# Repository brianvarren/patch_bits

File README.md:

# patch_bits

**SDIY building blocks.** Tiny helper boards that that make quick prototyping fun and easy.

---

## What is this?

A growing collection of hardware abstractions for recurring problems in mixed-signal synth DIY. My intent is to provide simple touch points: inputs, outputs, power, ground. Everything else should be refined, reliable boilerplate. Being fully open-hardware, these helpers can become reusable design blocks, to be implemented in larger custom synth PCBs or modules as you (or I) see fit.

---

## Philosophy

- Open-source hardware (CERN-OHL-W)
- Built for speed, not purity
- Easy to chain, mount, and mod

---

## A Note on Voltage & Signal Standards

For my personal builds, I decided some time ago to eschew Eurorack dual-rail power supplies and 10Vpp bipolar signals in favor of unipolar 0-3.3V DC-coupled MCU-friendly signals. I did this both out of frustration and laziness. My aim is to prototype quickly, learn in the process, and most of all, have fun. I found myself spending more time designing and debugging analog pre- and post- stages than I did designing the synths themselves. Some may argue that that is an important part of synth design; I can't argue. But, to me, a simplified, unipolar 3.3V signal format represents the freedom to explore without boundaries.

These helpers are designed to be compatible with both 3.3V and 5V systems. They may work with other single-rail voltages too (check the datasheets of the individual components).

Adapting to dual-rail supplies would require significant rework in most cases.

---

## Use it

- Build your own from the files
- Order from JLC
- Or [buy a prebuilt one](#) if you’re lazy or busy (no shame)

---

## License

CERN-OHL-W v2  
If you make changes and share them, cool. If you don’t, don’t sell them.

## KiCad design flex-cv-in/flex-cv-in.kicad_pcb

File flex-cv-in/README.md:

# Patch Bits: flex-cv-in

This board solves one big problem, and takes care of a handful of smaller ones along the way.

The big one is that RP2040 only gives you four ADC channels. That’s enough until you start designing synth modules and suddenly wish you had four CV inputs, each with a knob to offset or dial in a parameter manually. That’s the itch this board scratches.

flex-cv-in provides a footprint for a jack and a potentiometer. The knob and incoming CV are resistively summed into an inverting op-amp biased at mid-rail. The feedback resistor sets the gain to 2, restoring the original CV amplitude after averaging. The result is a stable, centered voltage where the knob sets a baseline and the CV input adds (or subtracts) modulation. That single output feeds one ADC channel.

Schottky diode clamps protect against over-voltage. There’s a dedicated jack detect pin designed for microcontrollers—pulled low when nothing’s inserted, floating high when a jack is present.

By default, the board runs in “bias” mode, which is ideal for parameters you want to sweep and modulate. But with two solder jumpers and a trace cut, you can reconfigure it into an attenuate mode. In that setup, the knob scales the incoming CV instead, centered around mid-rail. This is useful for things like linear FM, but the utility doesn’t stop there.

The board includes a low-pass RC filter on the output by default to tame ADC noise. If you want raw edges and wideband modulation, a labeled trace cut lets you disable that filter easily—no desoldering required.

It’s built for 3.3V or 5V single-supply systems, with short analog paths, proper biasing, and clean routing. It’s not calibrated, not meant for bipolar Eurorack signals, and not trying to be fancy. It just works—and it stays out of your way when you want to get creative.

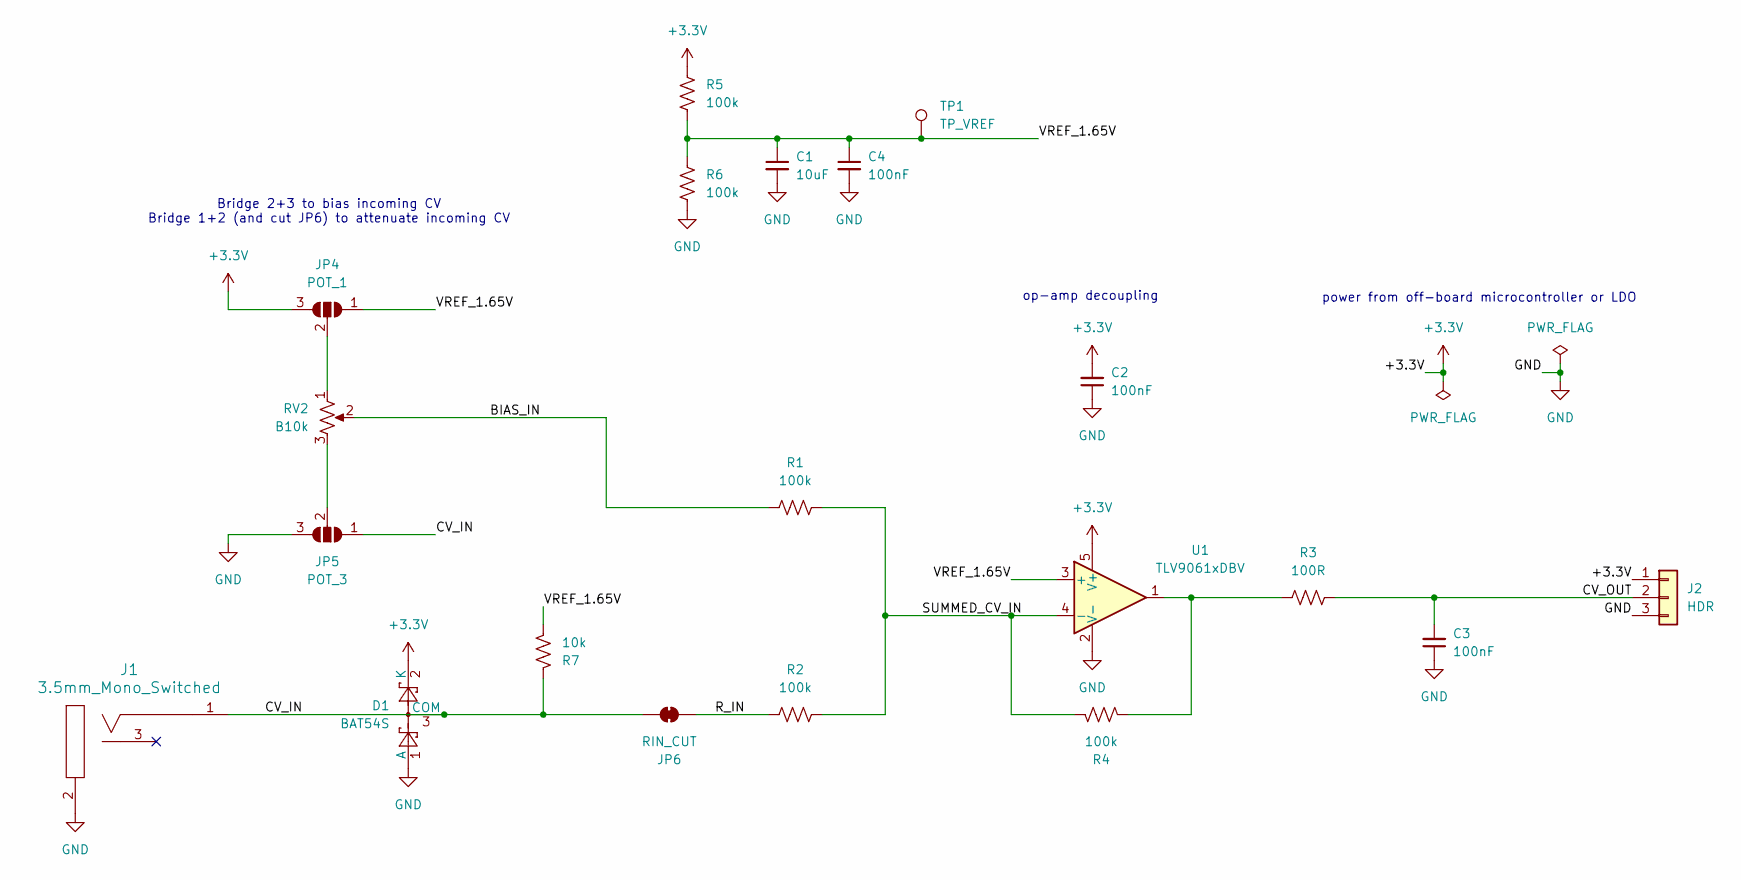
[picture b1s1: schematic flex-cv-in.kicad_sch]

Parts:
C1: 10uF; C_0805_2012Metric
C2, C3, C4: 100nF; C_0805_2012Metric
D1: BAT54S; SOT-23
J1: 3.5mm_Mono_Switched; EighthInch_PJ398SM; Part Number WQP-WQP518MA
J2: HDR; PinSocket_1x03_P2.54mm_Vertical
JP4: POT_1; SolderJumper-3_P1.3mm_Open_RoundedPad1.0x1.5mm
JP5: POT_3; SolderJumper-3_P1.3mm_Open_RoundedPad1.0x1.5mm
JP6: RIN_CUT; SolderJumper-2_P1.3mm_Bridged_RoundedPad1.0x1.5mm
R1, R2, R4, R5, R6: 100k; R_0805_2012Metric
R3: 100R; R_0805_2012Metric
R7: 10k; R_0805_2012Metric
RV2: B10k; Pot_9mm_Knurl_NoDet
TP1: TP_VREF; TestPoint_Pad_D1.5mm
U1: TLV9061xDBV; SOT-23-5

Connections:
+3.3V: C2.2, D1.2 (K), J2.1, JP4.3 (B), R5.1, U1.5 (V+)
/BIAS_IN: R1.1, RV2.2
/CV_IN: D1.3 (COM), J1.1 (SIG), JP5.1 (A), JP6.2 (B), R7.2
/CV_OUT: C3.2, J2.2, R3.2
/R_IN: JP6.1 (A), R2.1
/SUMMED_CV_IN: R1.2, R2.2, R4.1, U1.4 (-)
/VREF_1.65V: C1.1, C4.1, JP4.1 (A), R5.2, R6.1, R7.1, TP1.1, U1.3 (+)
GND: C1.2, C2.1, C3.1, C4.2, D1.1 (A), J1.2 (SHEILD), J2.3, JP5.3 (B), R6.2, U1.2 (V-)
unnamed: JP4.2 (C), RV2.1
unnamed: JP5.2 (C), RV2.3
unnamed: R3.1, R4.2, U1.1

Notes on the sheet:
op-amp decoupling
power from off-board microcontroller or LDO
Bridge 2+3 to bias incoming CV Bridge 1+2 (and cut JP6) to attenuate incoming CV

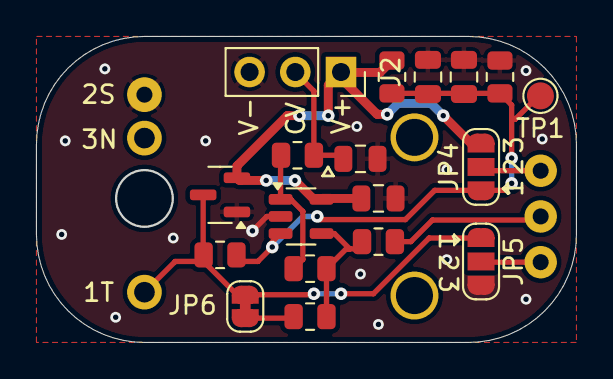
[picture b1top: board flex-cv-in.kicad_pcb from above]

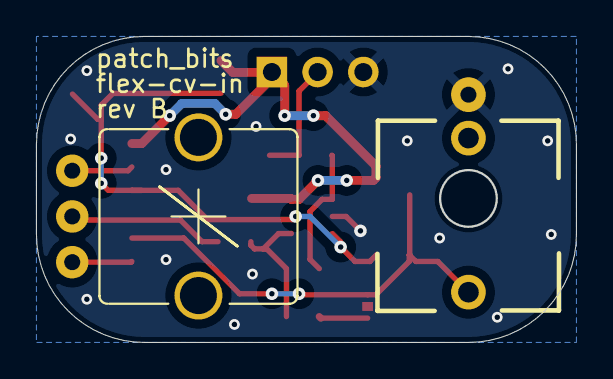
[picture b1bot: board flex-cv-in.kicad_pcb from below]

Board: 2 copper layers, 29.9 x 16.9 mm, 20 parts (2 on the bottom side), 11 nets.

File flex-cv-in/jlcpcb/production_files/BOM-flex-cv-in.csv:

Comment,Designator,Footprint,LCSC,Quantity
100k,R4,R_0805_2012Metric,,1
100nF,C3,C_0805_2012Metric,,1
HDR,J2,PinSocket_1x03_P2.54mm_Vertical,,1
10uF,C1,C_0805_2012Metric,,1
100k,R5,R_0805_2012Metric,,1
100k,R2,R_0805_2012Metric,,1
TLV9061xDBV,U1,SOT-23-5,,1
100k,R6,R_0805_2012Metric,,1
100nF,C2,C_0805_2012Metric,,1
BAT54S,D1,SOT-23,,1
100R,R3,R_0805_2012Metric,,1
100k,R1,R_0805_2012Metric,,1
100nF,C4,C_0805_2012Metric,,1
10k,R7,R_0805_2012Metric,,1

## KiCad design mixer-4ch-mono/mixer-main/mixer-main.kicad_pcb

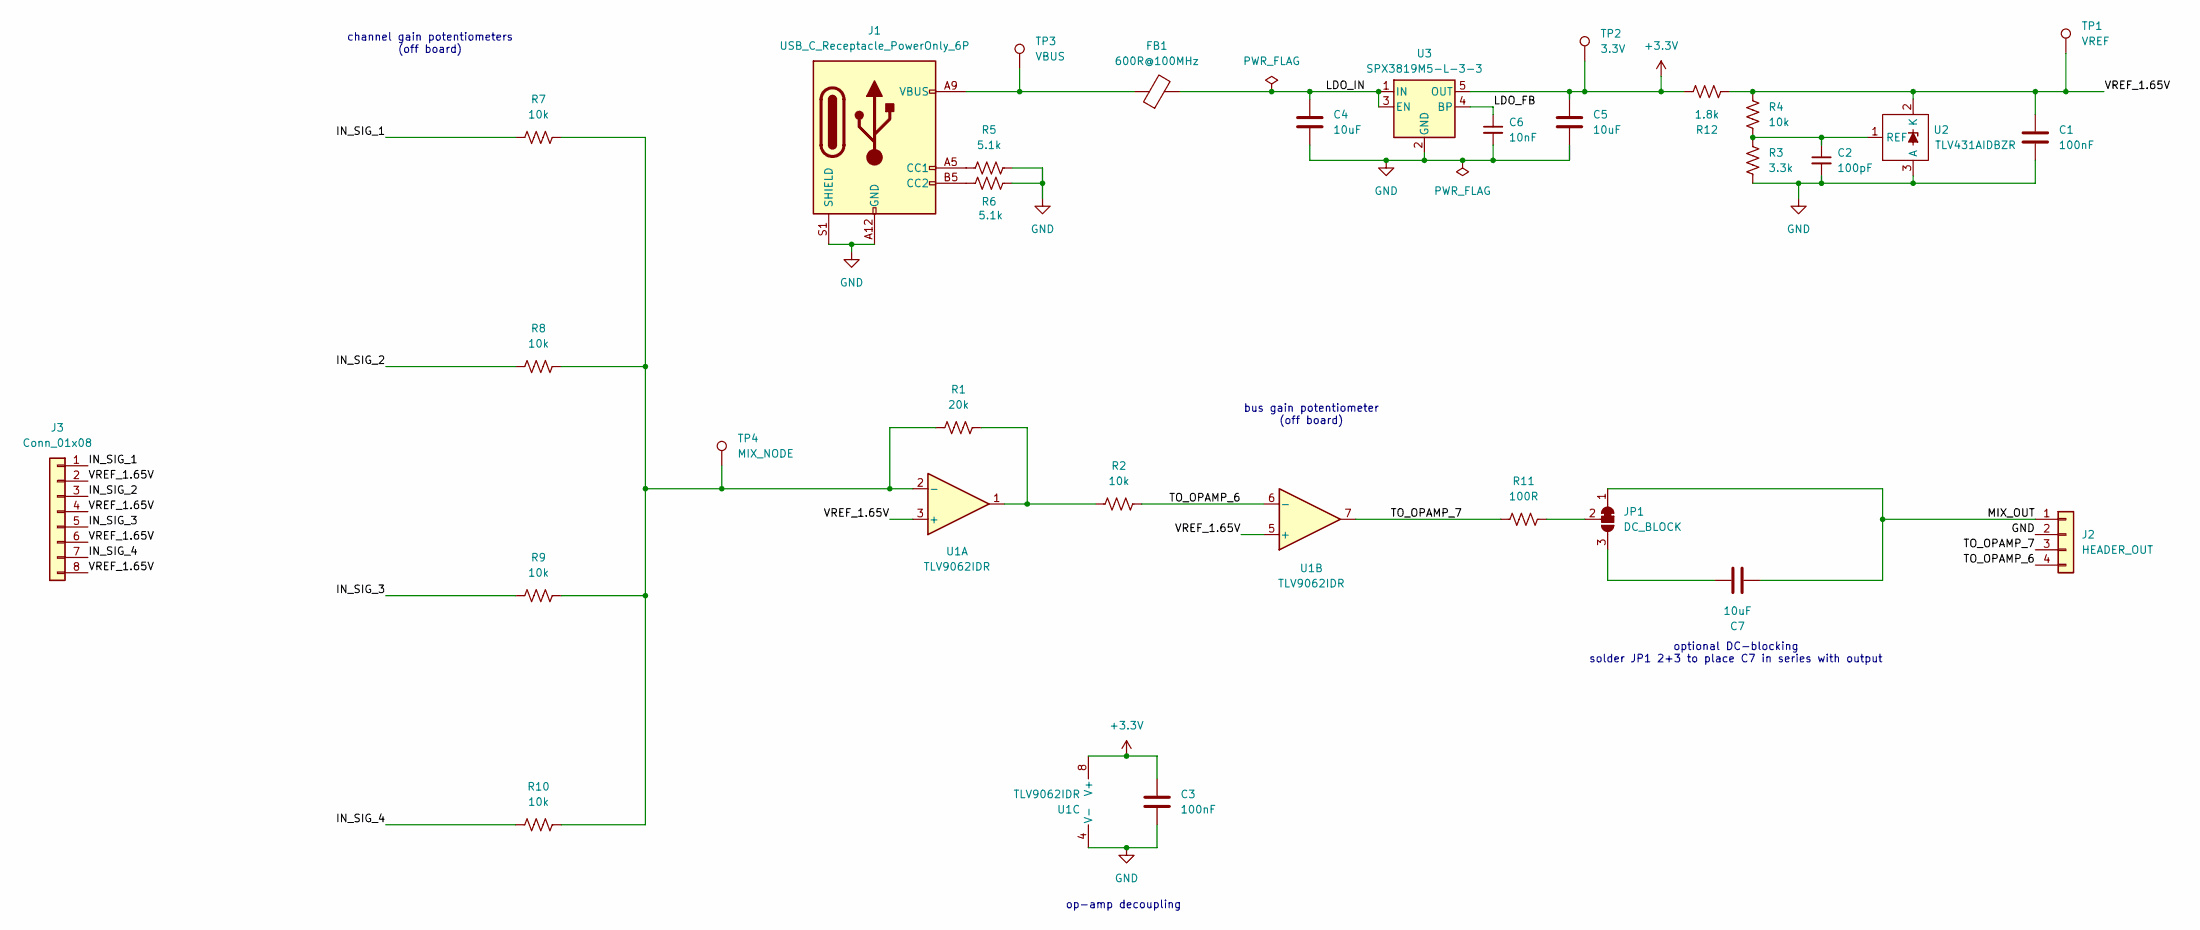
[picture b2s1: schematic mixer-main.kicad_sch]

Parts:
C1, C3: 100nF; C_0603_1608Metric
C2: 100pF; C_0603_1608Metric
C4, C5, C7: 10uF; C_1206_3216Metric
C6: 10nF; C_0805_2012Metric
FB1: 600R@100MHz; L_0805_2012Metric
J1: USB_C_Receptacle_PowerOnly_6P; USB_C_Receptacle_HRO_TYPE-C-31-M-17
J2: HEADER_OUT; PinHeader_1x04_P2.54mm_Vertical
J3: Conn_01x08; PinHeader_1x08_P2.54mm_Vertical
JP1: DC_BLOCK; SolderJumper-3_P1.3mm_Open_RoundedPad1.0x1.5mm
R1: 20k; R_0603_1608Metric
R2, R4, R7, R8, R9, R10: 10k; R_0603_1608Metric
R3: 3.3k; R_0603_1608Metric
R5, R6: 5.1k; R_0603_1608Metric
R11: 100R; R_0603_1608Metric
R12: 1.8k; R_0603_1608Metric
TP1: VREF; TestPoint_THTPad_D2.0mm_Drill1.0mm
TP2: 3.3V; TestPoint_THTPad_D2.0mm_Drill1.0mm
TP3: VBUS; TestPoint_THTPad_D2.0mm_Drill1.0mm
TP4: MIX_NODE; TestPoint_THTPad_D2.0mm_Drill1.0mm
U1: TLV9062IDR; SOIC-8_3.9x4.9mm_P1.27mm
U2: TLV431AIDBZR; SOT-23-3
U3: SPX3819M5-L-3-3; SOT-23-5

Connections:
+3.3V: C3.1, C5.1, R12.1, TP2.1, U1.8 (V+), U3.5 (OUT)
/IN_SIG_1: J3.1, R7.1
/IN_SIG_2: J3.3, R8.1
/IN_SIG_3: J3.5, R9.1
/IN_SIG_4: J3.7, R10.1
/LDO_FB: C6.1, U3.4 (BP)
/LDO_IN: C4.1, FB1.2, U3.1 (IN), U3.3 (EN)
/MIX_OUT: C7.1, J2.1, JP1.1 (A)
/TO_OPAMP_6: J2.4, R2.2, U1.6 (-)
/TO_OPAMP_7: J2.3, R11.1, U1.7
/VREF_1.65V: C1.1, J3.2, J3.4, J3.6, J3.8, R4.1, R12.2, TP1.1, U1.3 (+), U1.5 (+), U2.2 (K)
GND: C1.2, C2.2, C3.2, C4.2, C5.2, C6.2, J1.A12 (GND), J1.B12 (GND), J1.S1 (SHIELD), J2.2, R3.2, R5.2, R6.2, U1.4 (V-), U2.3 (A), U3.2 (GND)
unnamed: FB1.1, J1.A9 (VBUS), J1.B9 (VBUS), TP3.1
unnamed: J1.A5 (CC1), R5.1
unnamed: J1.B5 (CC2), R6.1
unnamed: C7.2, JP1.3 (B)
unnamed: JP1.2 (C), R11.2
unnamed: R1.2, R2.1, U1.1
unnamed: R1.1, R7.2, R8.2, R9.2, R10.2, TP4.1, U1.2 (-)
unnamed: C2.1, R3.1, R4.2, U2.1 (REF)

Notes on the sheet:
bus gain potentiometer (off board)
channel gain potentiometers (off board)
op-amp decoupling
optional DC-blocking solder JP1 2+3 to place C7 in series with output

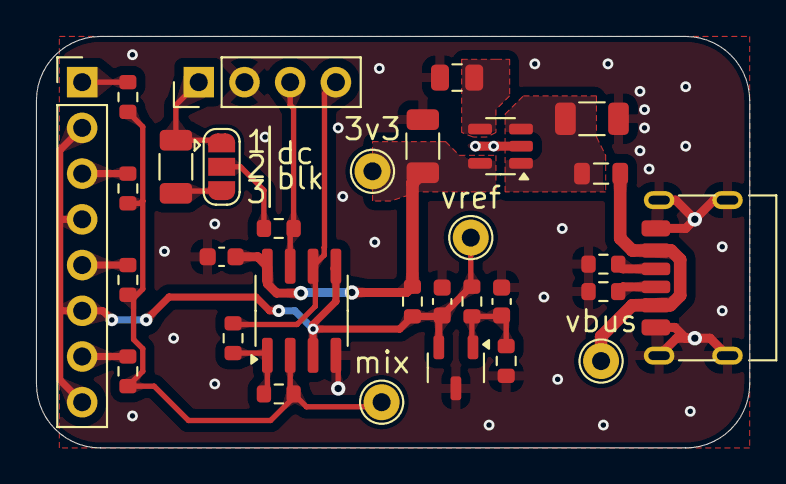
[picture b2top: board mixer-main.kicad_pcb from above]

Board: 2 copper layers, 39.6 x 22.9 mm, 31 parts (0 on the bottom side), 20 nets.

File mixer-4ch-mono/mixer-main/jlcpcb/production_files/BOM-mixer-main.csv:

Comment,Designator,Footprint,LCSC,Quantity
10nF,C6,C_0805_2012Metric,,1
10k,R8,R_0603_1608Metric,,1
20k,R1,R_0603_1608Metric,,1
3.3k,R3,R_0603_1608Metric,,1
10uF,C4,C_1206_3216Metric,,1
10uF,C7,C_1206_3216Metric,,1
USB_C_Receptacle_PowerOnly_6P,J1,USB_C_Receptacle_HRO_TYPE-C-31-M-17,,1
5.1k,R5,R_0603_1608Metric,,1
10k,R10,R_0603_1608Metric,,1
1.8k,R12,R_0603_1608Metric,,1
10k,R2,R_0603_1608Metric,,1
10k,R4,R_0603_1608Metric,,1
5.1k,R6,R_0603_1608Metric,,1
100nF,C1,C_0603_1608Metric,,1
10k,R7,R_0603_1608Metric,,1
TLV431AIDBZR,U2,SOT-23-3,,1
10k,R9,R_0603_1608Metric,,1
600R@100MHz,FB1,L_0805_2012Metric,,1
SPX3819M5-L-3-3,U3,SOT-23-5,,1
100pF,C2,C_0603_1608Metric,,1
10uF,C5,C_1206_3216Metric,,1
100nF,C3,C_0603_1608Metric,,1
100R,R11,R_0603_1608Metric,,1
TLV9062IDR,U1,SOIC-8_3.9x4.9mm_P1.27mm,,1

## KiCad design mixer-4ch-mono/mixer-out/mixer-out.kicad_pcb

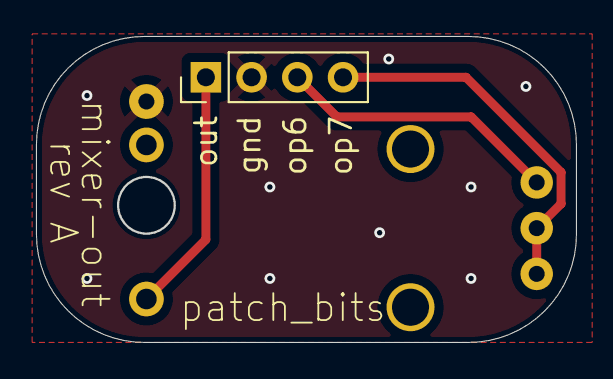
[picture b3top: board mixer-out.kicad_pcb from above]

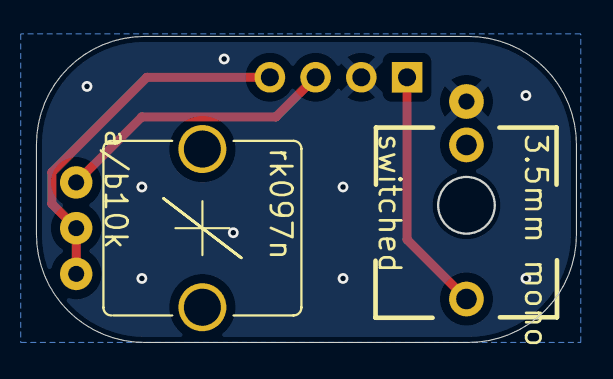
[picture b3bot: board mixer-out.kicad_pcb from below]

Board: 2 copper layers, 29.9 x 16.9 mm, 3 parts (2 on the bottom side), 4 nets.

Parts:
J1: 3.5mm_Mono_Switched; EighthInch_PJ398SM
J3: Conn_01x04; PinHeader_1x04_P2.54mm_Vertical
RV1: a/b10k; Pot_9mm_Knurl_NoDet

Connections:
/MIX_OUT: J1.1 (SIG), J3.1
/TO_OPAMP_6: J3.3, RV1.1
/TO_OPAMP_7: J3.4, RV1.2, RV1.3
GND: J1.2 (SHEILD), J3.2

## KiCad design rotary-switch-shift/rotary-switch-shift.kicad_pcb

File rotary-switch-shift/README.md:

# Patch Bits: rotary-switch-shift

This one allows you to mount a rotary switch of single or dual poles, up to eight positions, and read the switch position from three GPIO pins via shift register.

10k pullup resistors keep the switch contacts high until they are pulled to ground by turning the knob. The shift register reads each contact in parallel and shifts the result out when commanded by your sketch.

When using a dual pole switch, since two simultaneous connections will be made, you must deal with the simultaneous low bits in software.

I'll post an example sketch once I can verify these work.

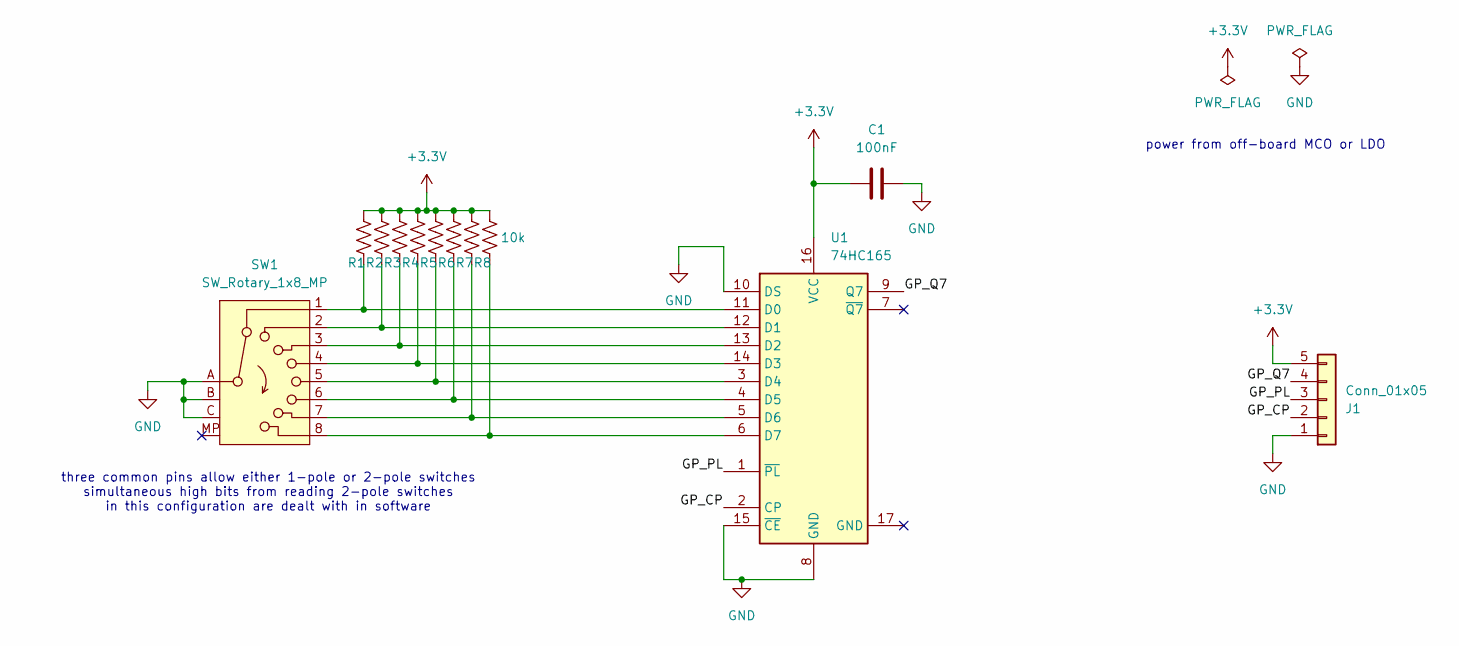
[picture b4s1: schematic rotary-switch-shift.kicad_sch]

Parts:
C1: 100nF; C_0805_2012Metric
J1: Conn_01x05; PinHeader_1x05_P2.54mm_Vertical
R1, R2, R3, R4, R5, R6, R7, R8: 10k; R_0805_2012Metric
SW1: SW_Rotary_1x8_MP; Switch_Rotary_SR16_1P8T_16mm
U1: 74HC165; DHVQFN-16-1EP_2.5x3.5mm_P0.5mm_EP1x2mm

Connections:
+3.3V: C1.1, J1.5, R1.2, R2.2, R3.2, R4.2, R5.2, R6.2, R7.2, R8.2, U1.16 (VCC)
/GP_CP: J1.2, U1.2 (CP)
/GP_PL: J1.3, U1.1 (~PL)
/GP_Q7: J1.4, U1.9 (Q7)
GND: C1.2, J1.1, SW1.A (Common), SW1.B (Common), SW1.C (Common), U1.8 (GND), U1.10 (DS), U1.15 (~CE)
unnamed: R1.1, SW1.1, U1.11 (D0)
unnamed: R2.1, SW1.2, U1.12 (D1)
unnamed: R3.1, SW1.3, U1.13 (D2)
unnamed: R4.1, SW1.4, U1.14 (D3)
unnamed: R5.1, SW1.5, U1.3 (D4)
unnamed: R6.1, SW1.6, U1.4 (D5)
unnamed: R7.1, SW1.7, U1.5 (D6)
unnamed: R8.1, SW1.8, U1.6 (D7)

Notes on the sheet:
three common pins allow either 1-pole or 2-pole switches simultaneous high bits from reading 2-pole switches in this configuration are dealt with in software
power from off-board MCO or LDO

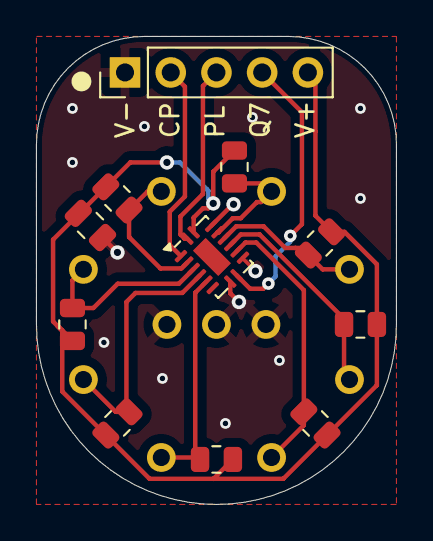
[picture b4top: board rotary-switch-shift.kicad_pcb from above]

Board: 2 copper layers, 20.0 x 26.0 mm, 12 parts (1 on the bottom side), 13 nets.

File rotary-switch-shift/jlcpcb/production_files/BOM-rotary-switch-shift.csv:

Comment,Designator,Footprint,LCSC,Quantity
10k,R2,R_0805_2012Metric,,1
74HC165,U1,DHVQFN-16-1EP_2.5x3.5mm_P0.5mm_EP1x2mm,,1
10k,R5,R_0805_2012Metric,,1
10k,R1,R_0805_2012Metric,,1
10k,R7,R_0805_2012Metric,,1
10k,R6,R_0805_2012Metric,,1
10k,R3,R_0805_2012Metric,,1
10k,R4,R_0805_2012Metric,,1
100nF,C1,C_0805_2012Metric,,1
10k,R8,R_0805_2012Metric,,1

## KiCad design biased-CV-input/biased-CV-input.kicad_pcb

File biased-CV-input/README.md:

# patch_bits // biased-cv-input

**SDIY building block for clean CV-to-ADC conversion with potentiometer bias.**  
This tiny PCB lets you mix a unipolar 0–3.3V CV signal with a DC bias from a panel-mounted potentiometer, buffer it with a low-noise op-amp, and send it cleanly into your microcontroller’s ADC—perfect for applications like linear FM, CV-controlled modulation depths, and more.

## 🔧 Features

- 📎 Mixes CV signal and knob-generated bias voltage
- 🎛️ Pot directly mounts to PCB for tight panel integration
- 🔌 Accepts unipolar PWM or CV input (0–3.3V range)
- 🧠 Buffered via TLV9061 (low-noise, rail-to-rail op amp)
- 🌊 AC-coupled output removes DC bias—ideal for FM signals
- 🔒 Input protection via Schottky diode and current-limiting resistor
- 🧷 Optional jumpers for jack normalization and CV detect

---

## 🧪 Use Case: Linear FM

This circuit is especially useful when you're feeding a sine wave or other modulator into an ADC for **linear frequency modulation**. The onboard AC coupling ensures **no DC bias slips through**, preserving pitch integrity and ensuring your FM stays clean and musically locked.

---

## 📦 Pinout (J2 Header)

| Pin | Signal        | Description                          |
|-----|---------------|--------------------------------------|
| 1   | +3.3V         | Power (shared with system 3.3V rail) |
| 2   | `JACK_DETECT` | Optional logic detect (pulled LOW when jack inserted) |
| 3   | `OUT`         | AC-coupled output to ADC input       |
| 4   | GND           | Ground                               |

---

## 🛠️ Panel Wiring

- Mount a standard 9mm 10k linear pot directly to the board.
- Wire `OUT` to any 3.3V-capable microcontroller ADC pin (e.g., RP2040).
- Send unipolar PWM or CV (0–3.3V) into the jack.
- Adjust bias with the pot to tune modulation range.
- Add optional logic via `JACK_DETECT` pin.

---

## 🧰 Specs

| Component     | Value / Notes                          |
|---------------|----------------------------------------|
| Op Amp        | TLV9061 (SOT-23-5, rail-to-rail)       |
| Potentiometer | 10k linear, 9mm panel mount            |
| Input Filter  | 100nF bypass cap (optional)            |
| AC Coupling   | 100nF ceramic cap to ground            |
| Output Resistor | 100Ω series for safety + filtering   |
| Diode         | BAT54S Schottky clamp to 3.3V/GND      |

---

## 🔓 License

This project is open-source under the **CERN-OHL-W** license.  
You’re free to remix, manufacture, and sell your own versions.  
If you do, give credit and consider supporting the original creator.

---

## 🧯 Safety Notes

This circuit is designed for **3.3V systems only**.  
Do **not** use with ±12V Eurorack signals without modification.

---

## 📸 Photos & Demos

> _(Coming soon)_

---

Part of the **patch_bits** series — SDIY building blocks.

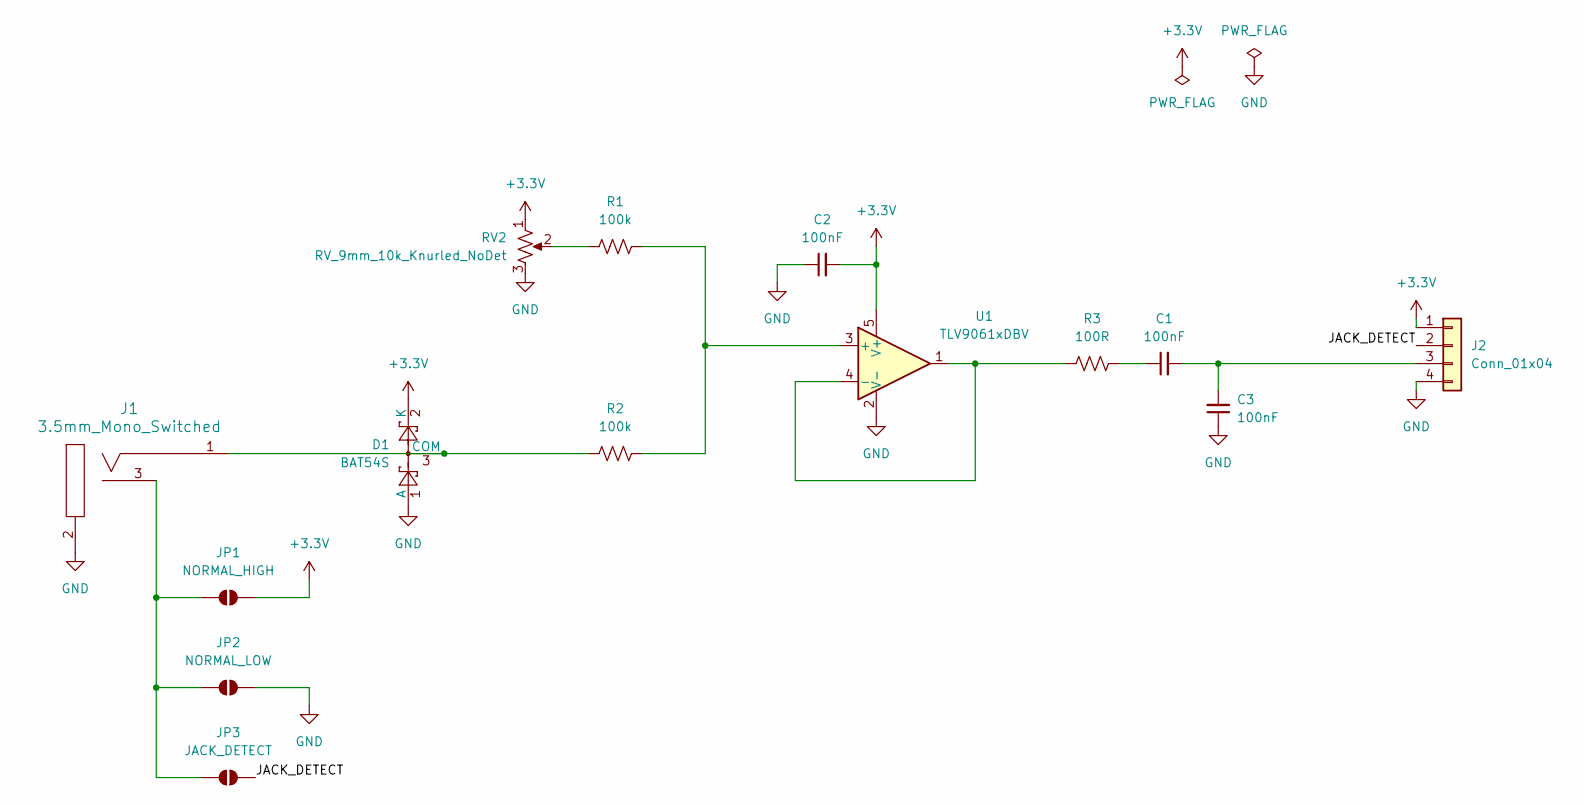
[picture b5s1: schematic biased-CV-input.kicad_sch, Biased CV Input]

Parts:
C1, C2, C3: 100nF; C_0805_2012Metric
D1: BAT54S; SOT-23
J1: 3.5mm_Mono_Switched; EighthInch_PJ398SM; Part Number WQP-WQP518MA
J2: Conn_01x04; PinHeader_1x04_P2.54mm_Vertical
JP1: NORMAL_HIGH; SolderJumper-2_P1.3mm_Open_TrianglePad1.0x1.5mm
JP2: NORMAL_LOW; SolderJumper-2_P1.3mm_Open_TrianglePad1.0x1.5mm
JP3: JACK_DETECT; SolderJumper-2_P1.3mm_Open_TrianglePad1.0x1.5mm
R1, R2: 100k; R_0805_2012Metric
R3: 100R; R_0805_2012Metric
RV2: RV_9mm_10k_Knurled_NoDet; Pot_9mm_Knurl_NoDet
U1: TLV9061xDBV; SOT-23-5

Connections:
+3.3V: C2.2, D1.2 (K), J2.1, JP1.2 (B), RV2.1, U1.5 (V+)
/CV: C1.2, C3.2, J2.3
/JACK_DETECT: J2.2, JP3.2 (B)
GND: C2.1, C3.1, D1.1 (A), J1.2 (SHEILD), J2.4, JP2.2 (B), RV2.3, U1.2 (V-)
unnamed: C1.1, R3.2
unnamed: D1.3 (COM), J1.1 (SIG), R2.1
unnamed: J1.3 (SW), JP1.1 (A), JP2.1 (A), JP3.1 (A)
unnamed: R1.1, RV2.2
unnamed: R1.2, R2.2, U1.3 (+)
unnamed: R3.1, U1.1, U1.4 (-)

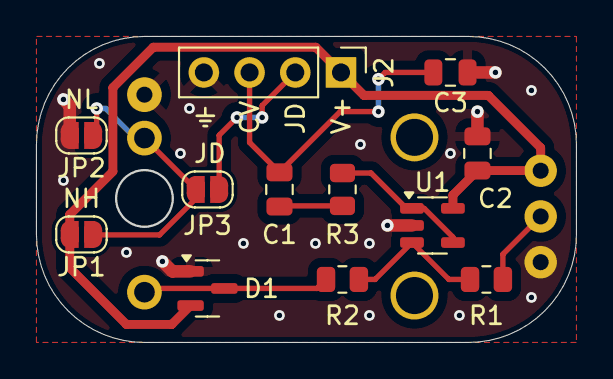
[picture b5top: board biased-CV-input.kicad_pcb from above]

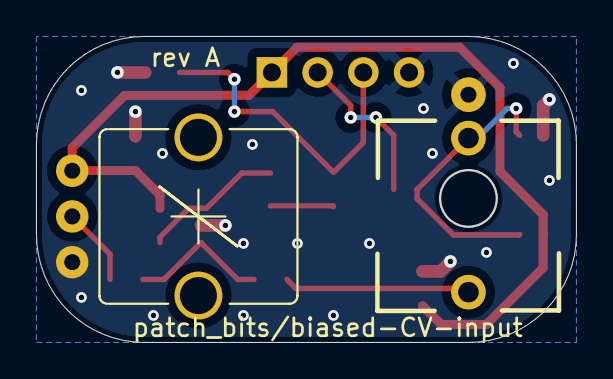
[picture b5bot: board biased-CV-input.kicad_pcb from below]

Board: 2 copper layers, 29.9 x 16.9 mm, 14 parts (2 on the bottom side), 10 nets.

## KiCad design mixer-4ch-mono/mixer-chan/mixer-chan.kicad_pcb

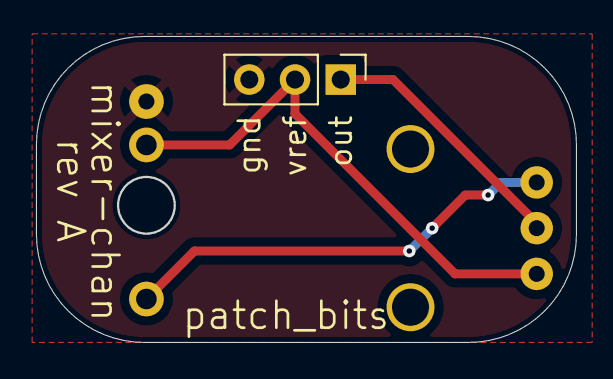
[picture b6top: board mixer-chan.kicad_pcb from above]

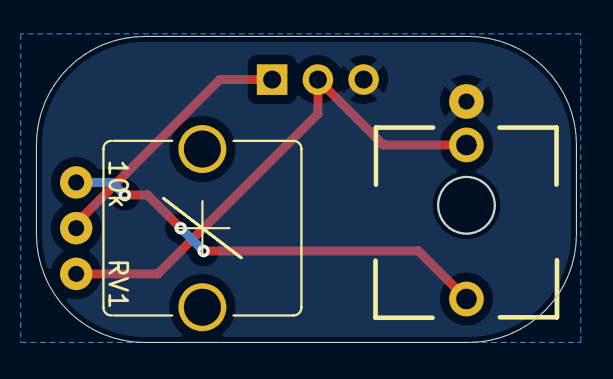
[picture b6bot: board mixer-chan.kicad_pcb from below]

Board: 2 copper layers, 29.9 x 16.9 mm, 3 parts (2 on the bottom side), 4 nets.

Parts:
J1: 3.5mm_Mono_Switched; EighthInch_PJ398SM
J2: Conn_01x03; PinHeader_1x03_P2.54mm_Vertical
RV1: 10k; Pot_9mm_Knurl_NoDet

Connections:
/VREF_1.65V: J1.3 (SW), J2.2, RV1.3
GND: J1.2 (SHEILD), J2.3
unnamed: J1.1 (SIG), RV1.1
unnamed: J2.1, RV1.2

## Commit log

2025-07-12 Publish biased-CV-input
    Lets you mix a unipolar 0–3.3V CV signal with a DC bias from a panel-mounted potentiometer, buffer it with a low-noise op-amp, and send it cleanly into your microcontroller’s ADC.
2025-07-12 Add BOM and SVG
2025-07-12 Update SVG
2025-07-12 Update image
2025-07-14 Add biased-CV-input-unity
2025-07-18 Rename and update flex-cv-in
2025-07-19 Update to final Rev. A
2025-07-19 Organization pass
2025-07-19 Cleanup
2025-07-21 Publish rotary-switch-shift rev A
2025-07-21 add WIP mixer-4ch-mono
2025-07-24 Separate mixer-out pcb
2025-07-26 Update mixer-main
    Continued with layout.
2025-07-27 Finalize mixer-4ch-mono rev. A
2025-08-01 flex-cv-in rev. B
    Updates and bug fixes:
    - Removed jack detect
    - Changed R7 connection from GND to VREF_1.65V
    - Connected JP5 pad 2 to RV2 pad 3
    - Adjusted layout of JP6 to avoid inadvertently cutting CV_IN trace
2025-08-01 Update flex-cv-in images and schematic
2025-08-01 update flex-cv-in images, gerbers to rev. B
2025-08-03 update JLC production files
